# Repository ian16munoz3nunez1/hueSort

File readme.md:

# HueSort

## Bibliografía y referencias

- [Arduino Documentation](https://docs.arduino.cc/language-reference/)
- [Arduino `abs` function](https://docs.arduino.cc/language-reference/en/functions/math/abs/)
- [Arduino `map` function](https://docs.arduino.cc/language-reference/en/functions/math/map/)
- [`analogWrite` function](https://docs.arduino.cc/language-reference/en/functions/analog-io/analogWrite/)
- [`analogWriteResolution` function](https://docs.arduino.cc/language-reference/en/functions/analog-io/analogWriteResolution/)
- [esp32 repository](https://github.com/espressif/arduino-esp32)
- [esp32 Guidebook](https://espressif-docs.readthedocs-hosted.com/projects/arduino-esp32/en/latest/)
- [esp32 installation guide](https://docs.espressif.com/projects/arduino-esp32/en/latest/installing.html)
- [esp32 PWM](https://randomnerdtutorials.com/esp32-pwm-arduino-ide/)
- [How to create a WiFi Access Point with esp32](https://www.upesy.com/blogs/tutorials/how-create-a-wifi-acces-point-with-esp32#)
- [How do I transfer an image taken by esp32cam over sockets](https://stackoverflow.com/questions/57823528/how-do-i-transfer-an-image-taken-by-esp32-cam-over-sockets)
- [esp32cam ov2640 camera settings](https://randomnerdtutorials.com/esp32-cam-ov2640-camera-settings/)

- [API Pins](https://gpiozero.readthedocs.io/en/stable/api_pins.html)
- [Use GPIO from Python](https://www.raspberrypi.com/documentation/computers/os.html#use-gpio-from-python)
- [Generating PWM in Raspberry Pi](https://forums.raspberrypi.com/viewtopic.php?t=358623)
- [Raspberry Pi y PWM](https://www.prometec.net/raspberry-y-pwm/)
- [FreeRTOS y Raspberry Pi OS](https://forums-raspberrypi-com.translate.goog/viewtopic.php?t=382519&_x_tr_sl=en&_x_tr_tl=es&_x_tr_hl=es&_x_tr_pto=tc)

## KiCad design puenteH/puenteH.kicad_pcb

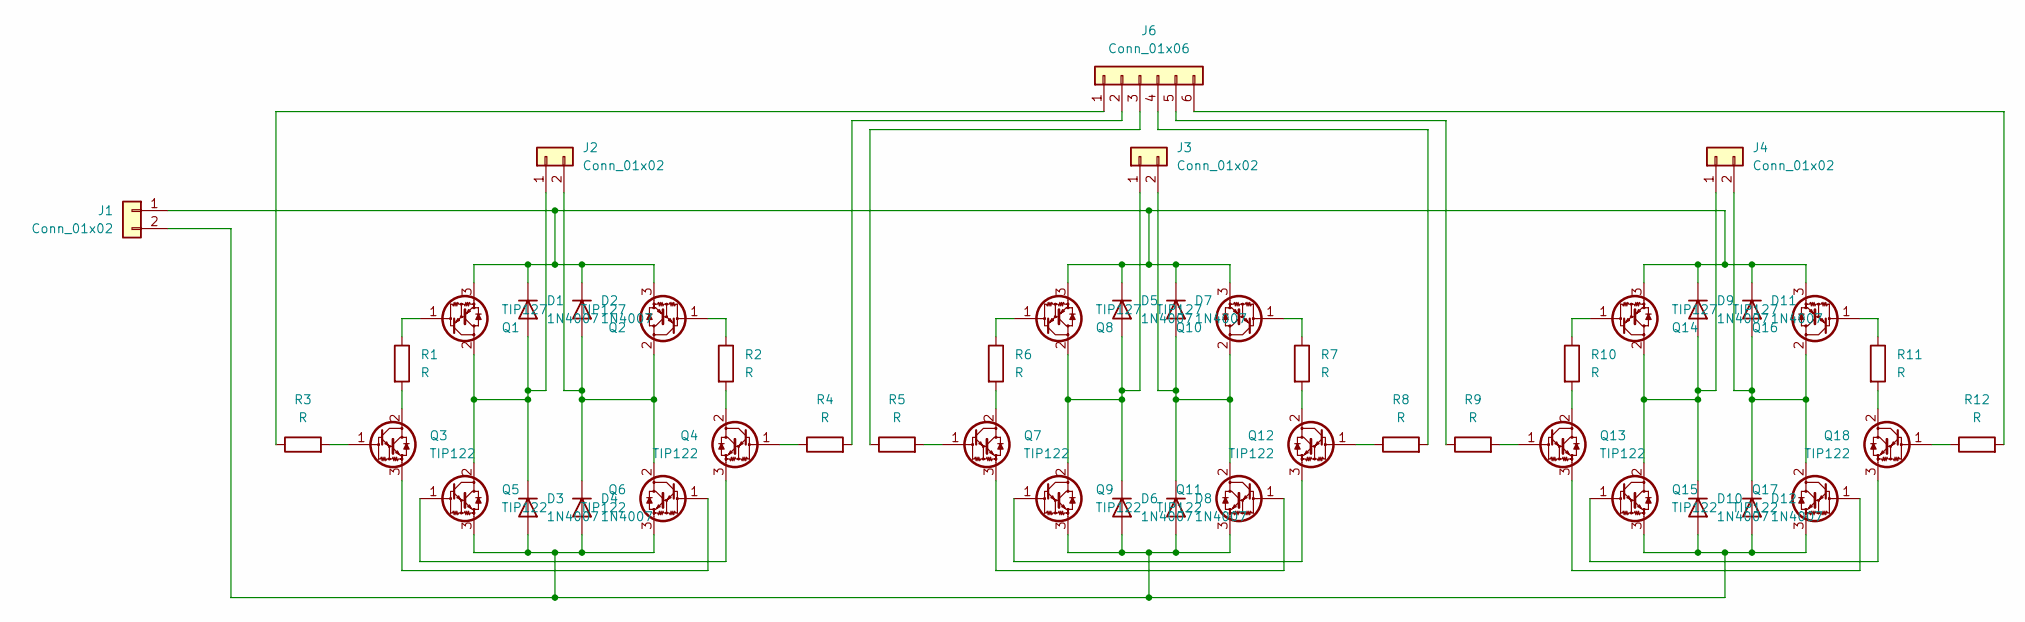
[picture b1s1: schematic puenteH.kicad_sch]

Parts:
D1, D2, D3, D4, D5, D6, D7, D8, D9, D10, D11, D12: 1N4007; D_DO-41_SOD81_P10.16mm_Horizontal
J1, J2, J3, J4: Conn_01x02; TerminalBlock_bornier-2_P5.08mm
J6: Conn_01x06; TerminalBlock_bornier-6_P5.08mm
Q1, Q2, Q8, Q10, Q14, Q16: TIP127; TO-220-3_Horizontal_TabDown
Q3, Q4, Q5, Q6, Q7, Q9, Q11, Q12, Q13, Q15, Q17, Q18: TIP122; TO-220-3_Horizontal_TabDown
R1, R2, R3, R4, R5, R6, R7, R8, R9, R10, R11, R12: R; R_Axial_DIN0207_L6.3mm_D2.5mm_P10.16mm_Horizontal

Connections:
unnamed: D1.2 (A), D3.1 (K), J2.1, Q1.2 (C), Q5.2 (C)
unnamed: D1.1 (K), D2.1 (K), D5.1 (K), D7.1 (K), D9.1 (K), D11.1 (K), J1.1, Q1.3 (E), Q2.3 (E), Q8.3 (E), Q10.3 (E), Q14.3 (E), Q16.3 (E)
unnamed: D2.2 (A), D4.1 (K), J2.2, Q2.2 (C), Q6.2 (C)
unnamed: D5.2 (A), D6.1 (K), J3.1, Q8.2 (C), Q9.2 (C)
unnamed: D7.2 (A), D8.1 (K), J3.2, Q10.2 (C), Q11.2 (C)
unnamed: D3.2 (A), D4.2 (A), D6.2 (A), D8.2 (A), D10.2 (A), D12.2 (A), J1.2, Q5.3 (E), Q6.3 (E), Q9.3 (E), Q11.3 (E), Q15.3 (E), Q17.3 (E)
unnamed: D9.2 (A), D10.1 (K), J4.1, Q14.2 (C), Q15.2 (C)
unnamed: D11.2 (A), D12.1 (K), J4.2, Q16.2 (C), Q17.2 (C)
unnamed: J6.1, R3.1
unnamed 10: J6.2, R4.2; also elsewhere on the board
unnamed 11: J6.3, R5.1; also elsewhere on the board
unnamed 12: J6.4, R8.2; also elsewhere on the board
unnamed 13: J6.5, R9.1; also elsewhere on the board
unnamed 14: J6.6, R12.2; also elsewhere on the board
unnamed: Q1.1 (B), R1.1
unnamed: Q2.1 (B), R2.1
unnamed 17: Q3.1 (B), R3.2; also elsewhere on the board
unnamed: Q3.2 (C), R1.2
unnamed: Q3.3 (E), Q6.1 (B)
unnamed: Q4.1 (B), R4.1
unnamed: Q4.2 (C), R2.2
unnamed: Q4.3 (E), Q5.1 (B)
unnamed: Q7.1 (B), R5.2
unnamed: Q7.2 (C), R6.2
unnamed: Q8.1 (B), R6.1
unnamed: Q10.1 (B), R7.1
unnamed: Q7.3 (E), Q11.1 (B)
unnamed: Q12.1 (B), R8.1
unnamed: Q12.2 (C), R7.2
unnamed: Q9.1 (B), Q12.3 (E)
unnamed: Q13.1 (B), R9.2
unnamed: Q13.2 (C), R10.2
unnamed: Q13.3 (E), Q17.1 (B)
unnamed: Q14.1 (B), R10.1
unnamed: Q15.1 (B), Q18.3 (E)
unnamed: Q16.1 (B), R11.1
unnamed: Q18.1 (B), R12.1
unnamed: Q18.2 (C), R11.2

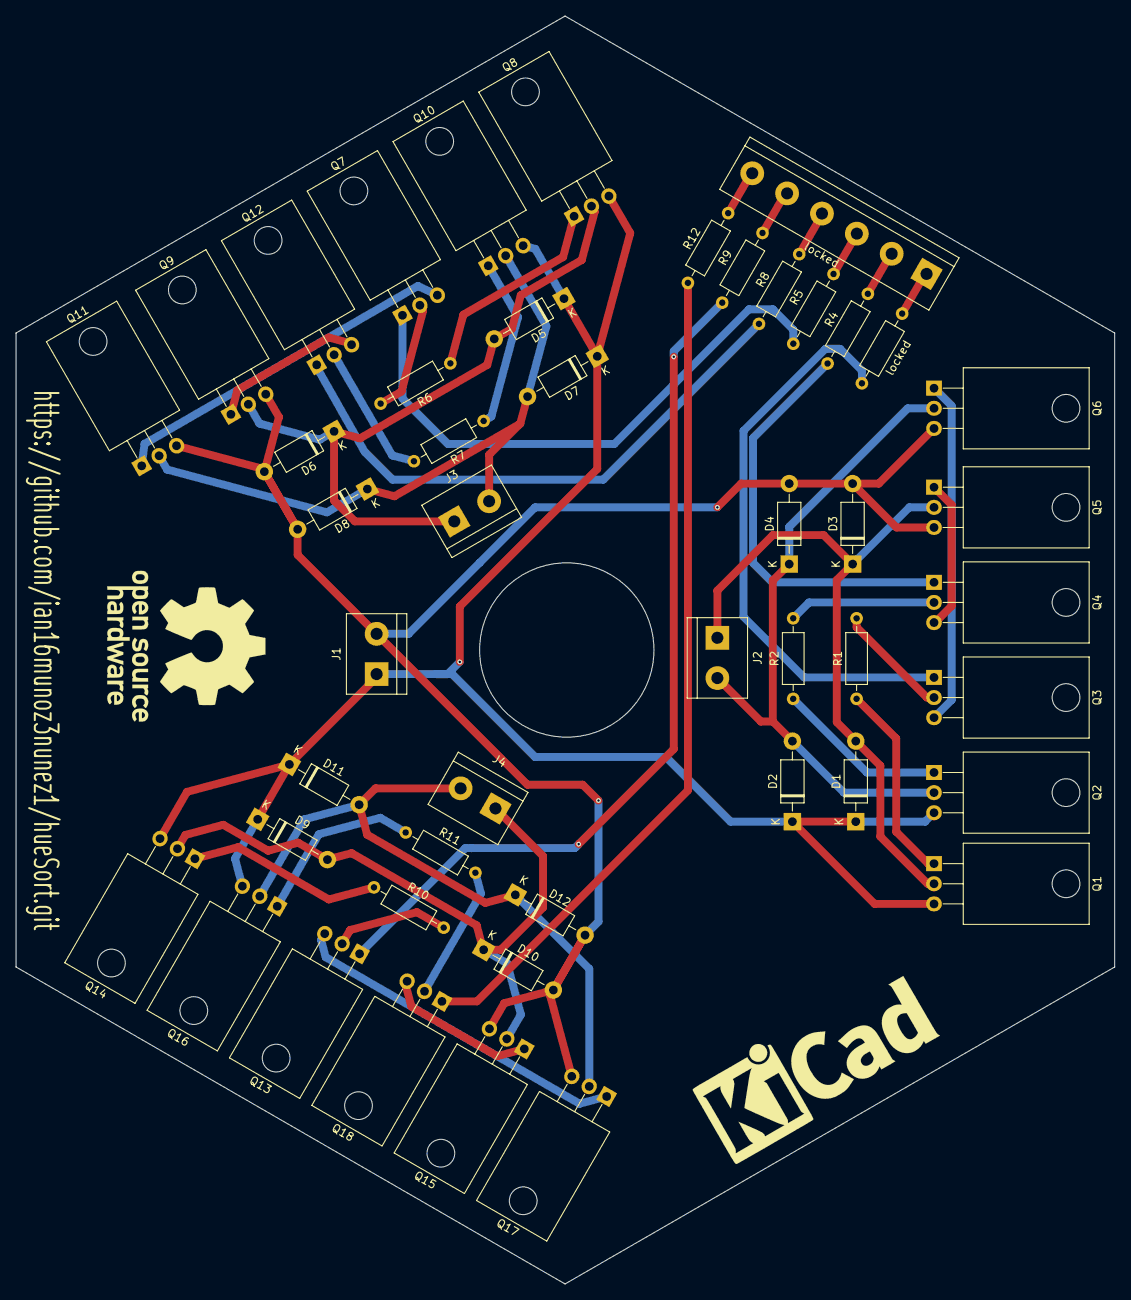
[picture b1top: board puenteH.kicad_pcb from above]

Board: 2 copper layers, 138.6 x 160.0 mm, 47 parts (0 on the bottom side), 38 nets.

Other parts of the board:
locked: Conn_01x06; TerminalBlock_bornier-6_P5.08mm
locked#2: locked; R_Axial_DIN0207_L6.3mm_D2.5mm_P10.16mm_Horizontal

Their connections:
unnamed: locked.1, locked#2.1
unnamed 10: locked.2; also elsewhere on the board
unnamed 11: locked.3; also elsewhere on the board
unnamed 12: locked.4; also elsewhere on the board
unnamed 13: locked.5; also elsewhere on the board
unnamed 14: locked.6; also elsewhere on the board
unnamed 17: locked#2.2; also elsewhere on the board

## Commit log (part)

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2025-08-25 Base requirements
    - 3D models to print
    - C and Python code for bot controlling
    - esp32cam application
    - MLP implementation to color recognition
    - Access Point for private network
    - Simulation to understand the project functionality
2025-08-25 3 references added to readme.md
2025-09-19 bot and esp32cam files updated
2025-09-19 Bibliografia en readme.md actualizada
2025-09-28 readme.md y documento
    - Nuevas referencias agregadas al archivo readme.md
    - Inicio de documentacion
2026-02-19 Base and pin blend files added to repo
2026-03-01 Modulo de eletronica y divisor de voltaje agregados a doc
2026-04-11 Changes in files for esp32 functionality
    - Deleted lines for print messages in motor.cpp file
    - PWM ranges for velocities changed in motor.cpp file
    - Last lines deleted in bot.ino, led.cpp and motor.cpp
    files
    - test.py file deleted, a new file will be added
2026-05-31 3D models printed and tested successfully
2026-06-08 bot/bot.ino file updated
    - Motor pins changed
    - Wi-Fi network updated to the Raspberry Pi one
    - IP addresses changed to the Raspberry Pi subnet
2026-06-08 Python robot files added
    - Classes, methods and functions working successfully in
    bot/robot.py file
    - bot/test.py file keep in repo
    - bot/dibujarMovil.py file added to show robot dimensions
    and pose
    - bot/main.py file added for an easier control of the robot
2026-06-08 H-Bridge design with KiCad added to repo
2026-06-08 Eletronic components list added to elecrtonics section in document
2026-06-17 Motor support design added to repo
2026-06-30 Lever design for servo motor added to repo
